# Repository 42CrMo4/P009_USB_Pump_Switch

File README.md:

# P009 USB Pump Switch

Home Assistant controlled ESP32-c3 USB Switch for "dump" USB Pumps for small scale gardening. 

## Description

This PCB uses one USB Power input to enable and disable two USB power poutputs.
To controll the output there is a ESP32-c3 that is able to be flashed with ESPhome (or Arduino) to be controlled via Home Assisstant. 
To switch the Power to the USB A Sockets the AP22804A IC is used. 
Input is an USB type C connector. 
This should drive cheap Aliaxpress pumps that are powered by USB and have only static delay and runtime optins. 

## Picture and BOM

| Font                                                                    | Back                                                                      |
|-------------------------------------------------------------------------|---------------------------------------------------------------------------|
|  |  |

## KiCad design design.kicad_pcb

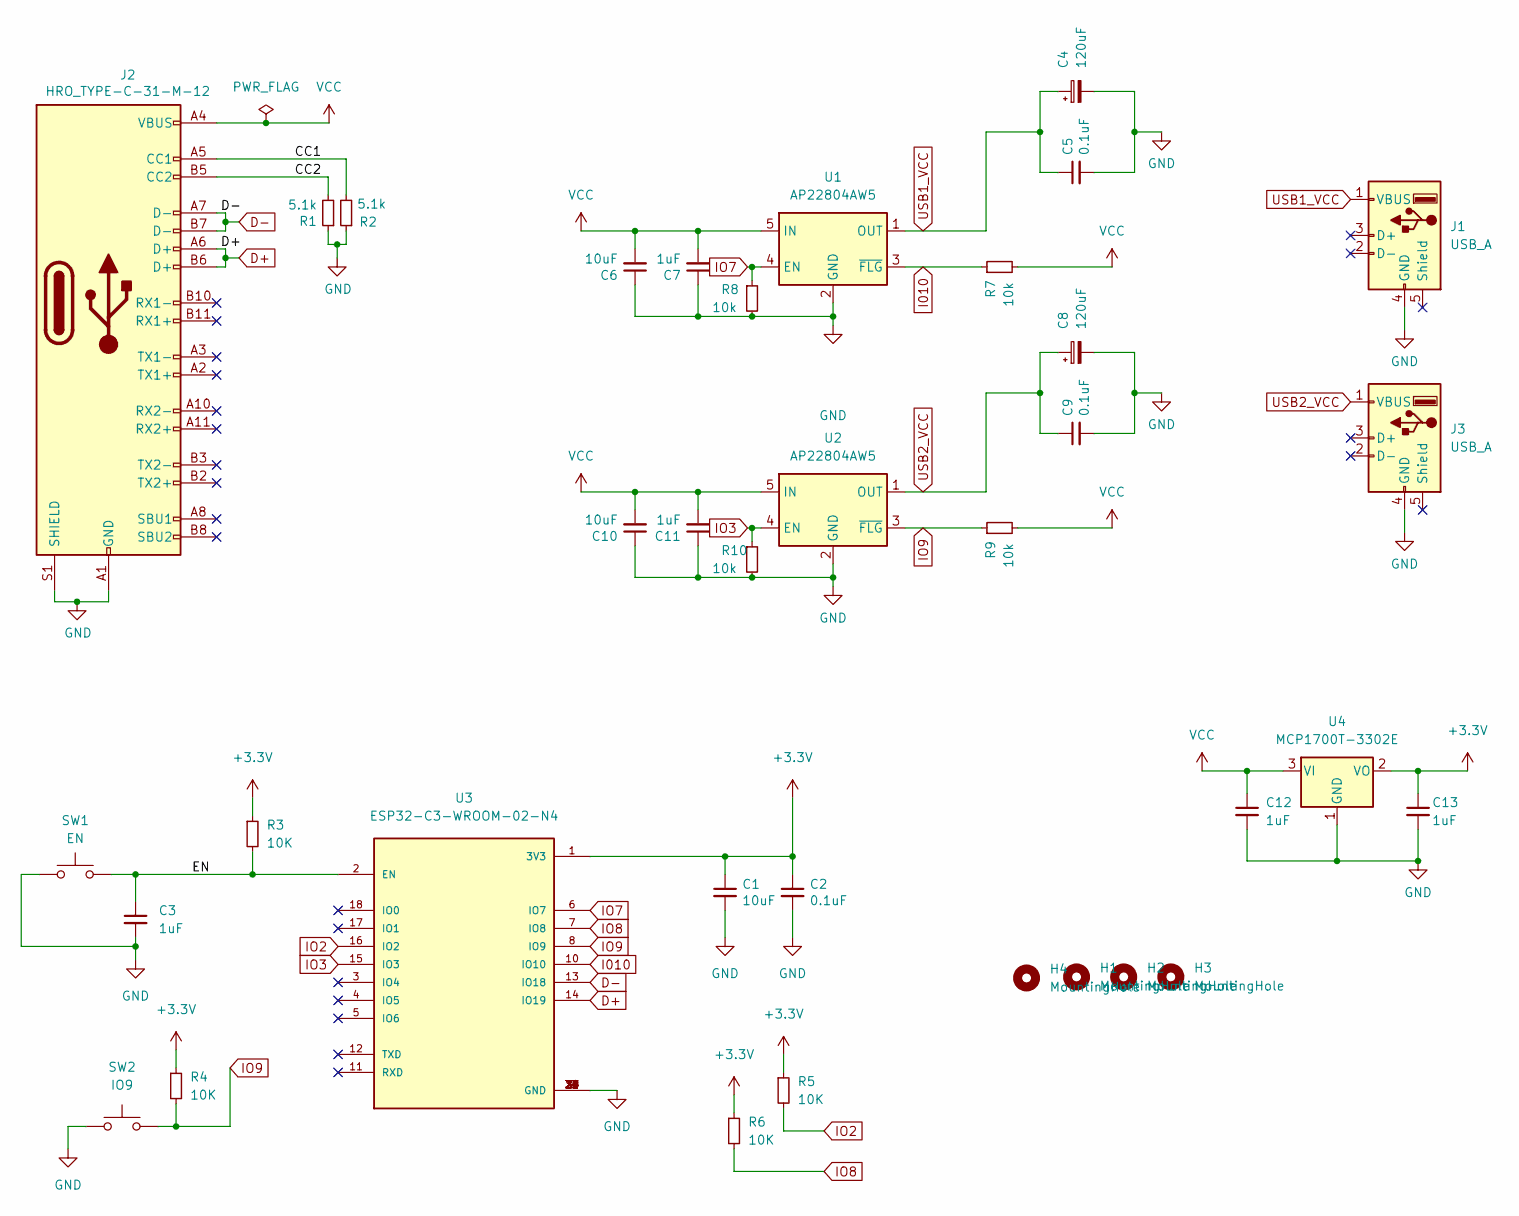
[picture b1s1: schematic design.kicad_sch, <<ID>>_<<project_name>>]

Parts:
C1, C6, C10: 10uF; C_0805_2012Metric
C2, C5, C9: 0.1uF; C_0805_2012Metric
C3, C7, C11, C12, C13: 1uF; C_0805_2012Metric
C4, C8: 120uF; CP_Radial_D8.0mm_P5.00mm
H1, H2, H3, H4: MountingHole; MountingHole_2.7mm_M2.5_Pad_Via
J1, J3: USB_A; USB_A_Stewart_SS-52100-001_Horizontal
J2: HRO_TYPE-C-31-M-12; USB_C_Receptacle_HRO_TYPE-C-31-M-12
R1, R2: 5.1k; R_0805_2012Metric
R3, R4, R5, R6: 10K; R_0805_2012Metric
R7, R8, R9, R10: 10k; R_0805_2012Metric
SW1: EN; SW_SPST_EVPBF
SW2: IO9; SW_SPST_EVPBF
U1, U2: AP22804AW5; SOT-23-5
U3: ESP32-C3-WROOM-02-N4; MODULE_ESP32-C3-WROOM-02-H4
U4: MCP1700T-3302E; SOT-23

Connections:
+3.3V: C1.1, C2.1, C13.1, R3.1, R4.1, R5.1, R6.1, U3.1 (3V3), U4.2 (VO)
/CC1: J2.A5 (CC1), R2.2
/CC2: J2.B5 (CC2), R1.2
/EN: C3.1, R3.2, SW1.2, U3.2 (EN)
D+: J2.A6 (D+), J2.B6 (D+), U3.14 (IO19)
D-: J2.A7 (D-), J2.B7 (D-), U3.13 (IO18)
GND: C1.2, C2.2, C3.2, C4.2, C5.2, C6.1, C7.1, C8.2, C9.2, C10.1, C11.1, C12.2, C13.2, J1.4 (GND), J2.A1 (GND), J2.A12 (GND), J2.B1 (GND), J2.B12 (GND), J2.S1 (SHIELD), J3.4 (GND), R1.1, R2.1, R8.2, R10.2, SW1.1, SW2.1, U1.2 (GND), U2.2 (GND), U3.9 (GND), U3.19 (GND), U3.20 (GND), U3.21 (GND), U3.22 (GND), U3.23 (GND), U3.24 (GND), U3.25 (GND), U3.26 (GND), U3.27 (GND), U3.28 (GND), U3.29 (GND), U3.30 (GND), U3.31 (GND), U3.32 (GND), U3.33 (GND), U3.34 (GND), U3.35 (GND), U3.36 (GND), U3.37 (GND), U3.38 (GND), U3.39 (GND), U4.1 (GND)
I010: R7.1, U1.3 (~FLG), U3.10 (IO10)
IO2: R5.2, U3.16 (IO2)
IO3: R10.1, U2.4 (EN), U3.15 (IO3)
IO7: R8.1, U1.4 (EN), U3.6 (IO7)
IO8: R6.2, U3.7 (IO8)
IO9: R4.2, R9.1, SW2.2, U2.3 (~FLG), U3.8 (IO9)
USB1_VCC: C4.1, C5.1, J1.1 (VBUS), U1.1 (OUT)
USB2_VCC: C8.1, C9.1, J3.1 (VBUS), U2.1 (OUT)
VCC: C6.2, C7.2, C10.2, C11.2, C12.1, J2.A4 (VBUS), J2.A9 (VBUS), J2.B4 (VBUS), J2.B9 (VBUS), R7.2, R9.2, U1.5 (IN), U2.5 (IN), U4.3 (VI)

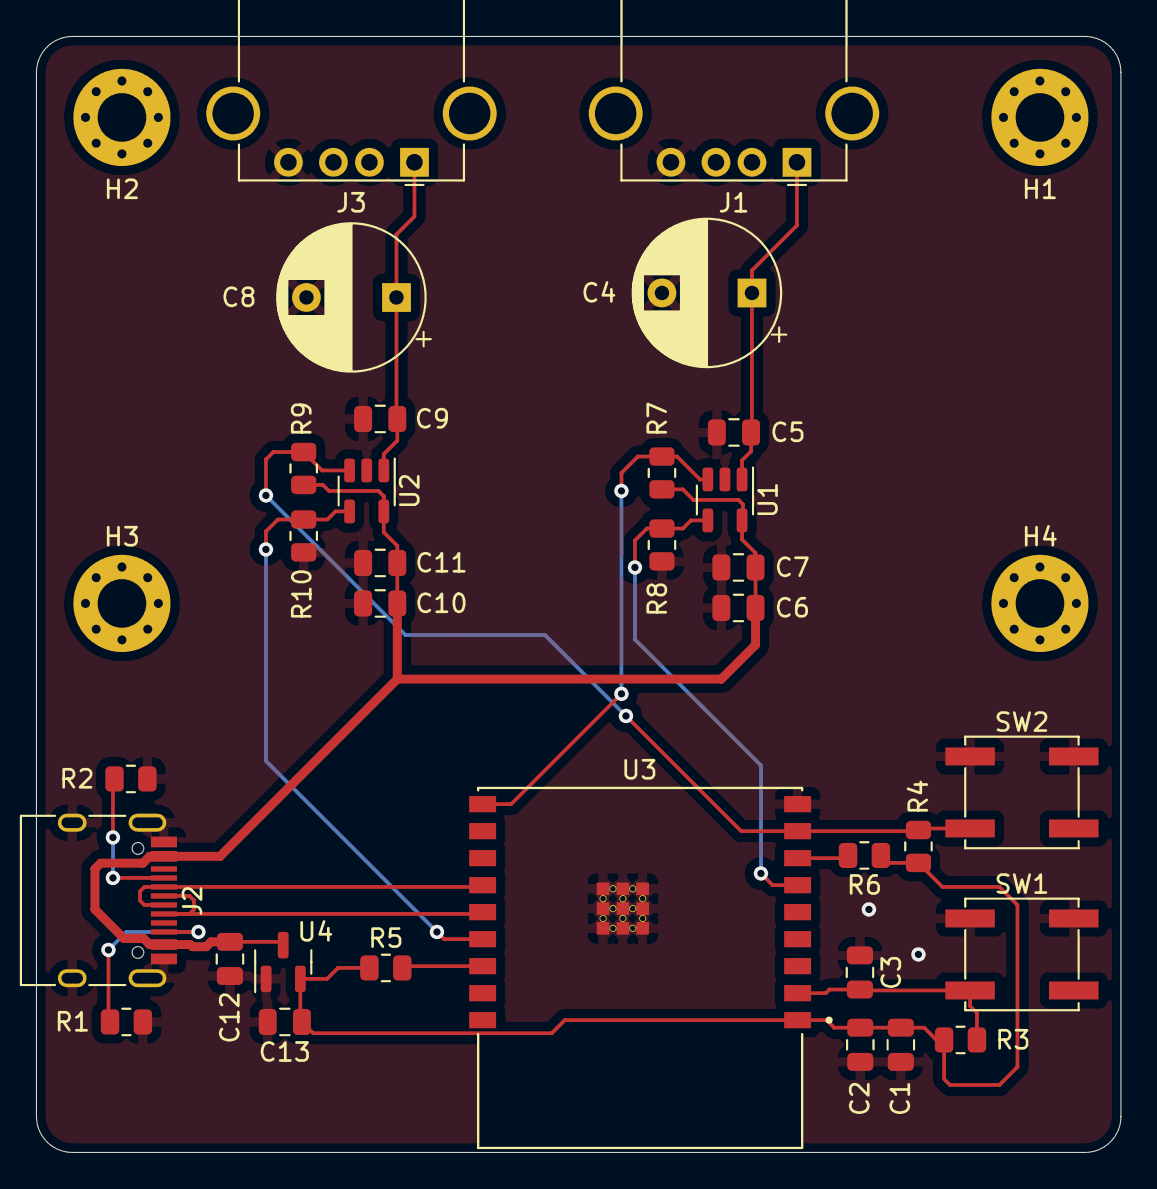
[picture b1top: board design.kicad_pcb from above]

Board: 2 copper layers, 60.2 x 62.0 mm, 36 parts (0 on the bottom side), 16 nets.

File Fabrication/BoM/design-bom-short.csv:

Row,Description,Part,References,Value,Footprint,Quantity Per PCB,Status,Datasheet,MF,AVAILABILITY,PRICE,PACKAGE,MP,PURCHASE-URL
1,"Unpolarized capacitor, small symbol",C_Small,C2 C5 C9,0.1uF,C_0805_2012Metric,3, ,~,,,,,,
2,"Unpolarized capacitor, small symbol",C_Small,C3 C7 C11 C12 C13,1uF,C_0805_2012Metric,5, ,~,,,,,,
3,"Unpolarized capacitor, small symbol",C_Small,C1 C6 C10,10uF,C_0805_2012Metric,3, ,~,,,,,,
4,"Polarized capacitor, small symbol",C_Polarized_Small,C4 C8,120uF,CP_Radial_D8.0mm_P5.00mm,2, ,~,,,,,,
5,USB Full-Featured Type-C Receptacle connector,USB_C_Receptacle,J2,HRO_TYPE-C-31-M-12,USB_C_Receptacle_HRO_TYPE-C-31-M-12,1, ,https://www.usb.org/sites/default/files/documents/usb_type-c.zip,,,,,,
6,USB Type A connector,USB_A,J1 J3,USB_A,USB_A_Stewart_SS-52100-001_Horizontal,2, , ~,,,,,,
7,"Resistor, small symbol",R_Small,R1 R2,5.1k,R_0805_2012Metric,2, ,~,,,,,,
8,"Resistor, small symbol",R_Small,R3 R4 R5 R6 R7 R8 R9 R10,10K,R_0805_2012Metric,8, ,~,,,,,,
9,"Push button switch, generic, two pins",SW_Push,SW1,EN,SW_SPST_EVPBF,1, ,~,,,,,,
10,"Push button switch, generic, two pins",SW_Push,SW2,IO9,SW_SPST_EVPBF,1, ,~,,,,,,
11,"Current limited 2.5A power switch, single channel, SOT-23-5",AP22804AW5,U1 U2,AP22804AW5,SOT-23-5,2, ,https://www.diodes.com/assets/Datasheets/AP22804_14.pdf,,,,,,
12,"WiFi Modules (802.11) (Engineering Samples) SMD module, ESP32-C3, 4MB SPI flash, PCB antenna, -40 C +105 C",ESP32-C3-WROOM-02-N4,U3,ESP32-C3-WROOM-02-N4,MODULE_ESP32-C3-WROOM-02-H4,1, ,,Espressif Systems,In Stock,None,Package,ESP32-C3-WROOM-02-H4,https://pricing.snapeda.com/search/part/ESP32-C3-WROOM-02-H4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
13,"250mA Low Quiscent Current LDO, 3.3V output, SOT-23",MCP1700-3302E_SOT23,U4,MCP1700T-3302E,SOT-23,1, ,http://ww1.microchip.com/downloads/en/DeviceDoc/20001826D.pdf,,,,,,

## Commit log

2023-06-03 init
2023-06-03 first do all renaming
2023-06-03 add <<date>> again
2023-06-04 DRC/ERC check
2023-06-04 Documentation
2023-06-05 add back variables for CI, rounded corners, mounting holes
2023-06-05 Update Bom and PCB_top
2023-06-05 Archive & Renew release docs
2024-01-07 typo
